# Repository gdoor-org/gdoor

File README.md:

<p align="center">
  https://gdoor-org.github.io/
</p>

_________________

The GDoor hardware adapter allows listening and controlling the bus and e.g. integrating a Gira door bell into a <b>smart home</b> like [Home Assistant](https://gdoor-org.github.io/documentation/homeassistant.html) or [openHAB](https://gdoor-org.github.io/documentation/openhab.html). It might serve as an DIY alternative to the Gira TKS-IP-Gateway. It supports the following features:

- (In development): Audio support via VOIP
- listening to the bus, e.g. to trigger notifications on mobile devices when a door bell button is pressed
- sending to the bus, e.g. to open the door

Receiving and sending video is currently neither supported nor plannend.

GDoor is a project to collect and document findings about the Gira Door System, all figured out by reverse engineering.
Contributions are welcome!

# Buy / DIY
Moved to the dedicated [page](https://gdoor-org.github.io/buy.html) on our homepage.

# Documentation / Home Automation
Moved to the dedicated [page](https://gdoor-org.github.io/documentation/getting-started.html) on our homepage.

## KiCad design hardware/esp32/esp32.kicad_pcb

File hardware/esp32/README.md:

More information about the firmware are located on the
[GDoor Homepage](https://gdoor-org.github.io/documentation/firmware.html).

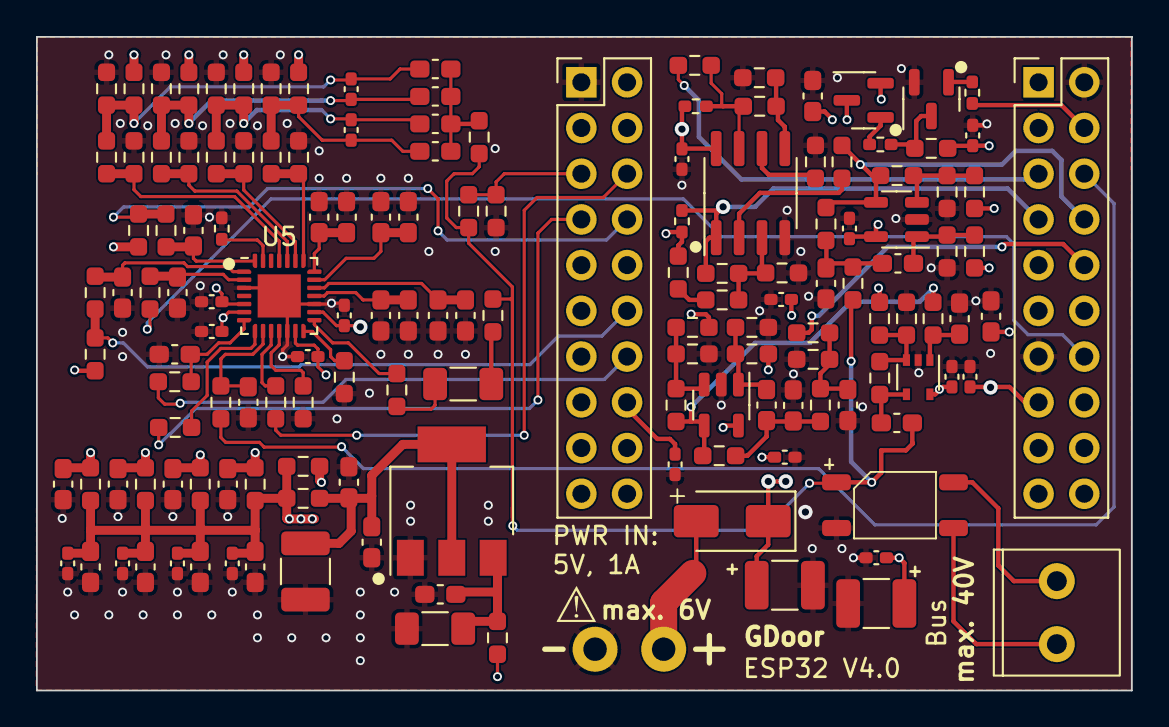
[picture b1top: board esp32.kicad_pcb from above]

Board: 4 copper layers, 60.8 x 36.3 mm, 151 parts (1 on the bottom side), 74 nets.

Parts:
C1: 47n; C_0603_1608Metric_Pad1.08x0.95mm_HandSolder
C2, C4, C8, C9, C18: 100p; C_0603_1608Metric_Pad1.08x0.95mm_HandSolder
C3, C5, C6, C7, C11, C13, C15, C16, C17, C36, C38, C40, C42, C46, C51, C53, C55, C62, C63: 100n; C_0402_1005Metric_Pad0.74x0.62mm_HandSolder
C10: 1n; C_0603_1608Metric_Pad1.08x0.95mm_HandSolder
C12, C14, C23, C25, C27, C28, C29, C30, C31, C35, C37, C39, C41, C43, C47, C52, C54, C56: 10u; C_0603_1608Metric_Pad1.08x0.95mm_HandSolder
C19, C20, C59: 100u; C_1210_3225Metric_Pad1.33x2.70mm_HandSolder
C21, C57: 10u; C_1206_3216Metric_Pad1.33x1.80mm_HandSolder
C22, C24, C26, C32, C33, C34: 100n; C_0603_1608Metric_Pad1.08x0.95mm_HandSolder
C44, C45, C48, C49, C50, C61: 22p; C_0603_1608Metric_Pad1.08x0.95mm_HandSolder
D1: MB10S; SOIC-4_4.55x3.7mm_P2.54mm
D2: SS14; D_SMA
J1: PlugIn_Terminal_Screw; anschlussklemme2x1_3_5
J2: ESP_left; PinHeader_2x10_P2.54mm_Vertical
J3: ESP_right; PinHeader_2x10_P2.54mm_Vertical
J4: PlugIn_Terminal_01x02; steckklemme2x1_dnp
Q1: MMBT5401; SOT-23
Q2: MMBT2222A; SOT-23
R1, R20: 130k; R_0603_1608Metric_Pad0.98x0.95mm_HandSolder
R2: 22k; R_0603_1608Metric_Pad0.98x0.95mm_HandSolder
R3, R4, R18, R19, R35: 82k; R_0603_1608Metric_Pad0.98x0.95mm_HandSolder
R5, R7, R16, R17: 5k1; R_0603_1608Metric_Pad0.98x0.95mm_HandSolder
R6, R10, R15, R22, R27, R33: 18k; R_0603_1608Metric_Pad0.98x0.95mm_HandSolder
R8, R13, R29, R31, R45: 10k; R_0402_1005Metric_Pad0.72x0.64mm_HandSolder
R9, R28, R30: 47k; R_0603_1608Metric_Pad0.98x0.95mm_HandSolder
R11, R23, R24, R73: 10k; R_0603_1608Metric_Pad0.98x0.95mm_HandSolder
R12, R25, R46, R47: 2k4; R_0603_1608Metric_Pad0.98x0.95mm_HandSolder
R14, R37, R38, R39, R40, R69, R70, R71, R72: 1k; R_0603_1608Metric_Pad0.98x0.95mm_HandSolder
R21, R26: 4k7; R_0603_1608Metric_Pad0.98x0.95mm_HandSolder
R32: 22; R_0603_1608Metric_Pad0.98x0.95mm_HandSolder
R34, R36, R55, R56, R57, R58, R59, R60, R61, R62, R63, R64, R65, R66, R67, R68, R74: 0; R_0603_1608Metric_Pad0.98x0.95mm_HandSolder
R41, R42, R43, R44, R50, R51, R52, R53, R54: 33; R_0603_1608Metric_Pad0.98x0.95mm_HandSolder
R48, R49: 100; R_0603_1608Metric_Pad0.98x0.95mm_HandSolder
S1: SYM_ESD_Small; ESD-Logo_6.6x6mm_SilkScreen
U: TLV9351; SOT-353_SC-70-5
U2, U3: LMV321; SOT-23-5
U4: ESP32_mini_no_pads
U5: ES8374; QFN-28-1EP_4x4mm_P0.45mm_EP2.4x2.4mm
U6: LM393; SOIC-8_3.9x4.9mm_P1.27mm
U7: AMS1117-3.3; SOT-223-3_TabPin2

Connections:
+3.3V: C6.1, C13.2, C14.2, C16.1, C17.1, C19.1, J2.16 (3V3), R3.2, R5.1, R25.1, R29.2, R31.2, R55.2, U2.5 (V+), U6.8 (V+)
+3.3V_ANA: C32.1, C59.1, C61.2, R58.2, U7.2 (VO)
+3.3V_AUDIO: C46.2, C47.2, C51.2, C52.2, C53.2, C54.2, C55.2, C56.2, R41.2, R42.2, R43.2, R44.2, R46.1, R47.1, R55.1, R58.1, R63.1, R64.1, R65.1, R66.1
+5V: C5.1, C11.2, C12.2, C20.1, D2.1 (K), J3.15 (VCC_(USB)), Q1.2 (E1), R9.2, R57.2
+5Vonoff: C3.1, C7.1, C15.1, Q1.3 (C1), R17.1, R18.2, R33.1, U.5 (V+), U3.5 (V+)
/BUS_DCVOLT: J2.5 (IO_39/SVN), R35.1, R73.1
/I2C_SCLK: J2.12 (IO_23/D7), R47.2, R48.1
/I2C_SDA: J2.8 (IO_18/D5), R46.2, R49.1
/I2S_ASDOUT: J2.7 (IO_35), R53.1
/I2S_DSDIN: J2.6 (IO_26/D0), R54.1
/I2S_LRCK: J3.6 (IO_25), R51.1
/I2S_MCLK: J3.14 (IO_00), R50.1
/I2S_SCLK: J2.14 (IO_05/D8), R52.1
/RX: J3.7 (IO_21/D2/SDA), R28.1, R29.1, U6.1
/RX_ANA: J3.8 (IO_32), R10.1, R12.1, R26.2, U2.4
/RX_DAC: J3.5 (IO_22/D1/SCL), R56.2
/TX: J3.10 (IO_12/TDI), R34.2
/TX_EN: J3.4 (IO_27), R13.2
GND: C2.1, C3.2, C5.2, C6.2, C7.2, C9.1, C10.1, C11.1, C12.1, C13.1, C14.1, C15.2, C16.2, C17.2, C18.1, C19.2, C20.2, C22.2, C23.1, C24.2, C25.1, C26.2, C27.1, C32.2, C33.2, C34.2, C35.1, C36.1, C37.1, C38.1, C39.1, C40.1, C41.1, C42.1, C43.1, C44.1, C45.1, C46.1, C47.1, C48.1, C49.1, C50.1, C51.1, C52.1, C53.1, C54.1, C55.1, C56.1, C57.1, C59.2, C61.1, D1.2 (-), J2.1 (GND), J3.2 (GND), J3.13 (GND), J4.1, Q2.2 (E), R4.1, R6.1, R7.1, R16.1, R19.1, R21.1, R22.2, R23.1, R27.2, R45.1, R59.1, R60.1, R61.1, R62.1, R67.1, R68.1, R69.1, R70.1, R71.1, R72.1, R73.2, U.2 (V-), U2.2 (V-), U3.2 (V-), U5.3 (DGND), U5.12 (SPKGND), U5.17 (AGND), U5.29 (EP), U6.4 (V-), U7.1 (GND)
unnamed: C1.1, R2.1, U.4
unnamed: C2.2, C4.2, R1.2, R10.2
unnamed: C8.2, C9.2, R15.2, R20.2
unnamed: C10.2, R20.1, R21.2, R34.1
unnamed: C21.1, R32.2
unnamed: C21.2, R36.1
unnamed: C28.1, C63.1, R37.1, R60.2, R63.2
unnamed: C28.2, C29.2, C30.2, C31.2, R74.2
unnamed: C29.1, C63.2, R38.1, R62.2, R66.2
unnamed: C30.1, C62.1, R39.1, R59.2, R64.2
unnamed: C31.1, C62.2, R40.1, R61.2, R65.2
unnamed: C1.2, D1.1 (+), R1.1, R35.2, R36.2, R74.1
unnamed: D2.2 (A), J4.2
unnamed: D1.4, J1.1
unnamed: D1.3, J1.2
unnamed: Q1.1 (B1), R8.1
unnamed: Q2.1 (B), R13.1
unnamed: Q2.3 (C), R8.2, R9.1
unnamed: R11.1, R14.1, R15.1, U3.4
unnamed: R24.2, R25.2
unnamed: R30.1, R31.1, R56.1, U6.7
unnamed: C18.2, R11.2, U.1 (+)
unnamed: R2.2, R6.2, R33.2, U.3 (-)
unnamed: C4.1, R3.1, R4.2, U2.1 (+)
unnamed: R5.2, R7.2, R12.2, U2.3 (-)
unnamed: C8.1, R18.1, R19.2, U3.1 (+)
unnamed: R14.2, R16.2, R17.2, U3.3 (-)
unnamed: C25.2, C26.1, U5.19 (ADCVREF)
unnamed: C27.2, C34.1, U5.18 (DACVREF)
unnamed: R37.2, R72.2, U5.24 (MIC1N)
unnamed: R38.2, R71.2, U5.25 (MIC1P)
unnamed: R39.2, R70.2, U5.22 (MIC2N)
unnamed: R40.2, R69.2, U5.23 (MIC2P)
unnamed: C22.1, C35.2, U5.21 (MICBIAS)
unnamed: R32.1, U5.15 (MONOOUT)
unnamed: R68.2, U5.11 (SPKN)
unnamed: R67.2, U5.14 (SPKP)
unnamed: C23.2, C24.1, U5.20 (VMID)
unnamed: C44.2, R48.2, U5.1 (CCLK)
unnamed: C45.2, R49.2, U5.28 (CDATA)
unnamed: R45.2, U5.27 (CE)
unnamed: R53.2, U5.8 (ASDOUT)
unnamed: R54.2, U5.10 (DSDIN)
unnamed: C49.2, R51.2, U5.9 (LRCK)
unnamed: C50.2, R50.2, U5.2 (MCLK)
unnamed: C48.2, R52.2, U5.7 (SCLK)
unnamed: C42.2, C43.2, R41.1, U5.16 (AVDD)
unnamed: C40.2, C41.2, R42.1, U5.6 (DVDD)
unnamed: C38.2, C39.2, R43.1, U5.5 (PVDD)
unnamed: C36.2, C37.2, R44.1, U5.13 (SPKVDD)
unnamed: R23.2, R24.1, R28.2, U6.3 (+)
unnamed: R26.1, U6.2 (-)
unnamed: R22.1, R30.2, U6.5 (+)
unnamed: R27.1, U6.6 (-)
unnamed: C33.1, C57.2, R57.1, U7.3 (VI)

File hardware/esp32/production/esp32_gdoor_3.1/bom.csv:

Designator,Footprint,Quantity,Value,LCSC Part #
C1,0603,1,47n,C1622
"C11, C13, C15, C16, C17, C3, C5, C6, C7",0402,9,100n,C307331
"C12, C14",0603,2,10u,C96446
"C19, C20",1210,2,100u,C15008
"C2, C4, C8, C9",0603,4,100p,C14858
D1,SOIC-4_4.55x3.7mm_P2.54mm,1,MB10S,C2488
D2,D_SMA,1,SS14,C2480
J1,steckklemme2x1_1,1,PlugIn_Terminal_01x02,C8387
J2,PinHeader_2x10_P2.54mm_Vertical,1,ESP_left,C7501280
J3,PinHeader_2x10_P2.54mm_Vertical,1,ESP_right,C7501280
J5,nofoorprint,1,Plugged into C8387,C8466
Q1,SOT-23,1,MMBT5401,C8326
Q2,SOT-23,1,MMBT2222A,C8512
"R1, R20",0603,2,130k,C22795
"R10, R15, R22, R33, R6",0603,5,18k,C25810
"R11, R23, R24",0603,3,10k,C25804
"R12, R25",0603,2,2k4,C22940
"R13, R29, R31, R8",0402,4,10k,C25744
R14,0603,1,1k,C21190
"R16, R17, R5, R7",0603,4,5k1,C23186
"R18, R19, R3, R4",0603,4,82k,C23254
R2,0603,1,22k,C31850
"R26, R27",0603,2,4k7,C23162
"R28, R30, R9",0603,3,47k,C25819
R32,0603,1,100k,C25803
R34,0603,1,0,C21189
U1,SOT-353_SC-70-5,1,TLV9351,C4367425
"U2, U3",SOT-23-5,2,LMV321,C7972
U6,SOIC-8_3.9x4.9mm_P1.27mm,1,LM393,C7955

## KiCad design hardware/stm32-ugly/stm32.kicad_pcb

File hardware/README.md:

# Content
> [!IMPORTANT]  
> Work in progress.
> The current hardware as shown here has a hardware bug:
> The high/low logic values of the ESP32 on the bus data receiving side are not
> respected. A comparator on Pin28 (GPIO32) is needed.
>
> The current firmware therefore decodes on Pin0 (IO12),
> as a manual hardware modification was added.

Simple adapter board for ESP32mini.
There are production files to get nearly fully assembled boards from http://jlcpcb.com under `esp32/production`.
A very rough guide how to order on http://jlcpcb.com is under https://www.youtube.com/watch?v=Y2G-SiKUJPk.

Additionally you will need:
- ESP32 Mini. E.g. from https://www.az-delivery.de/products/esp32-d1-mini
- 2x Stiftleiste 2,54mm 2x10 to solder into the adapter and connect the adapter PCB to the ESP32 Mini. E.g. https://www.reichelt.de/stiftleisten-2-54-mm-2x10-gerade-mpe-087-2-020-p119898.html

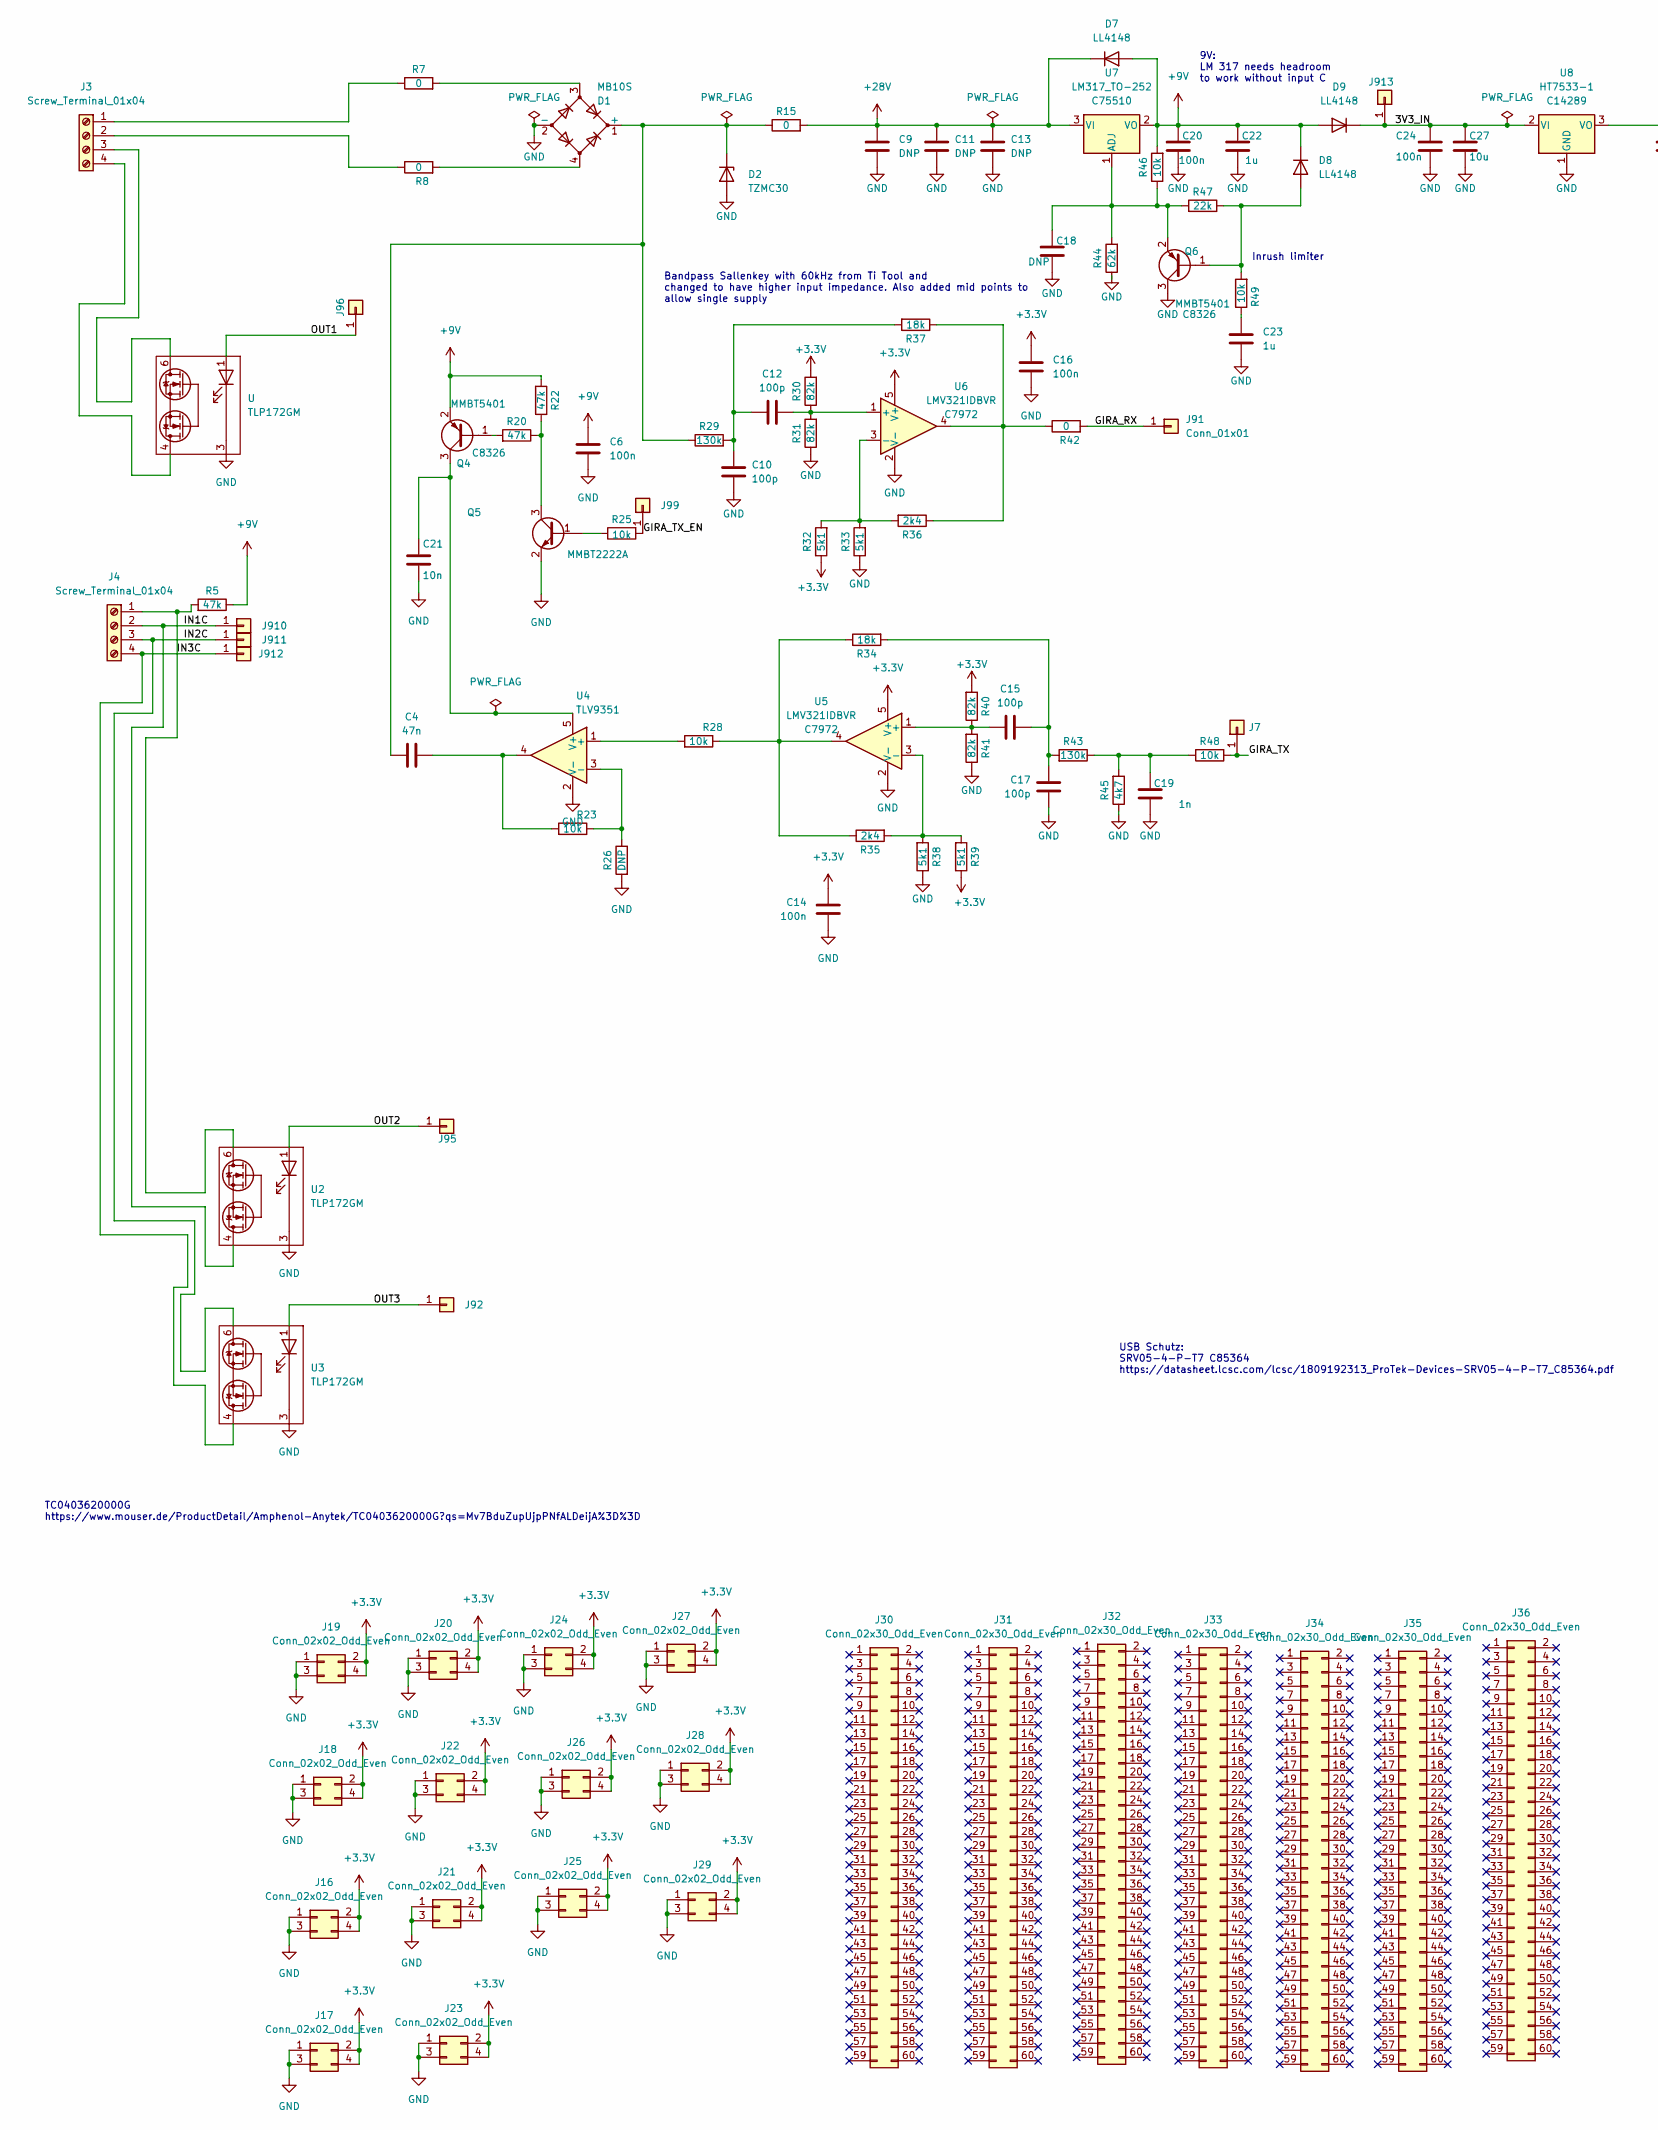
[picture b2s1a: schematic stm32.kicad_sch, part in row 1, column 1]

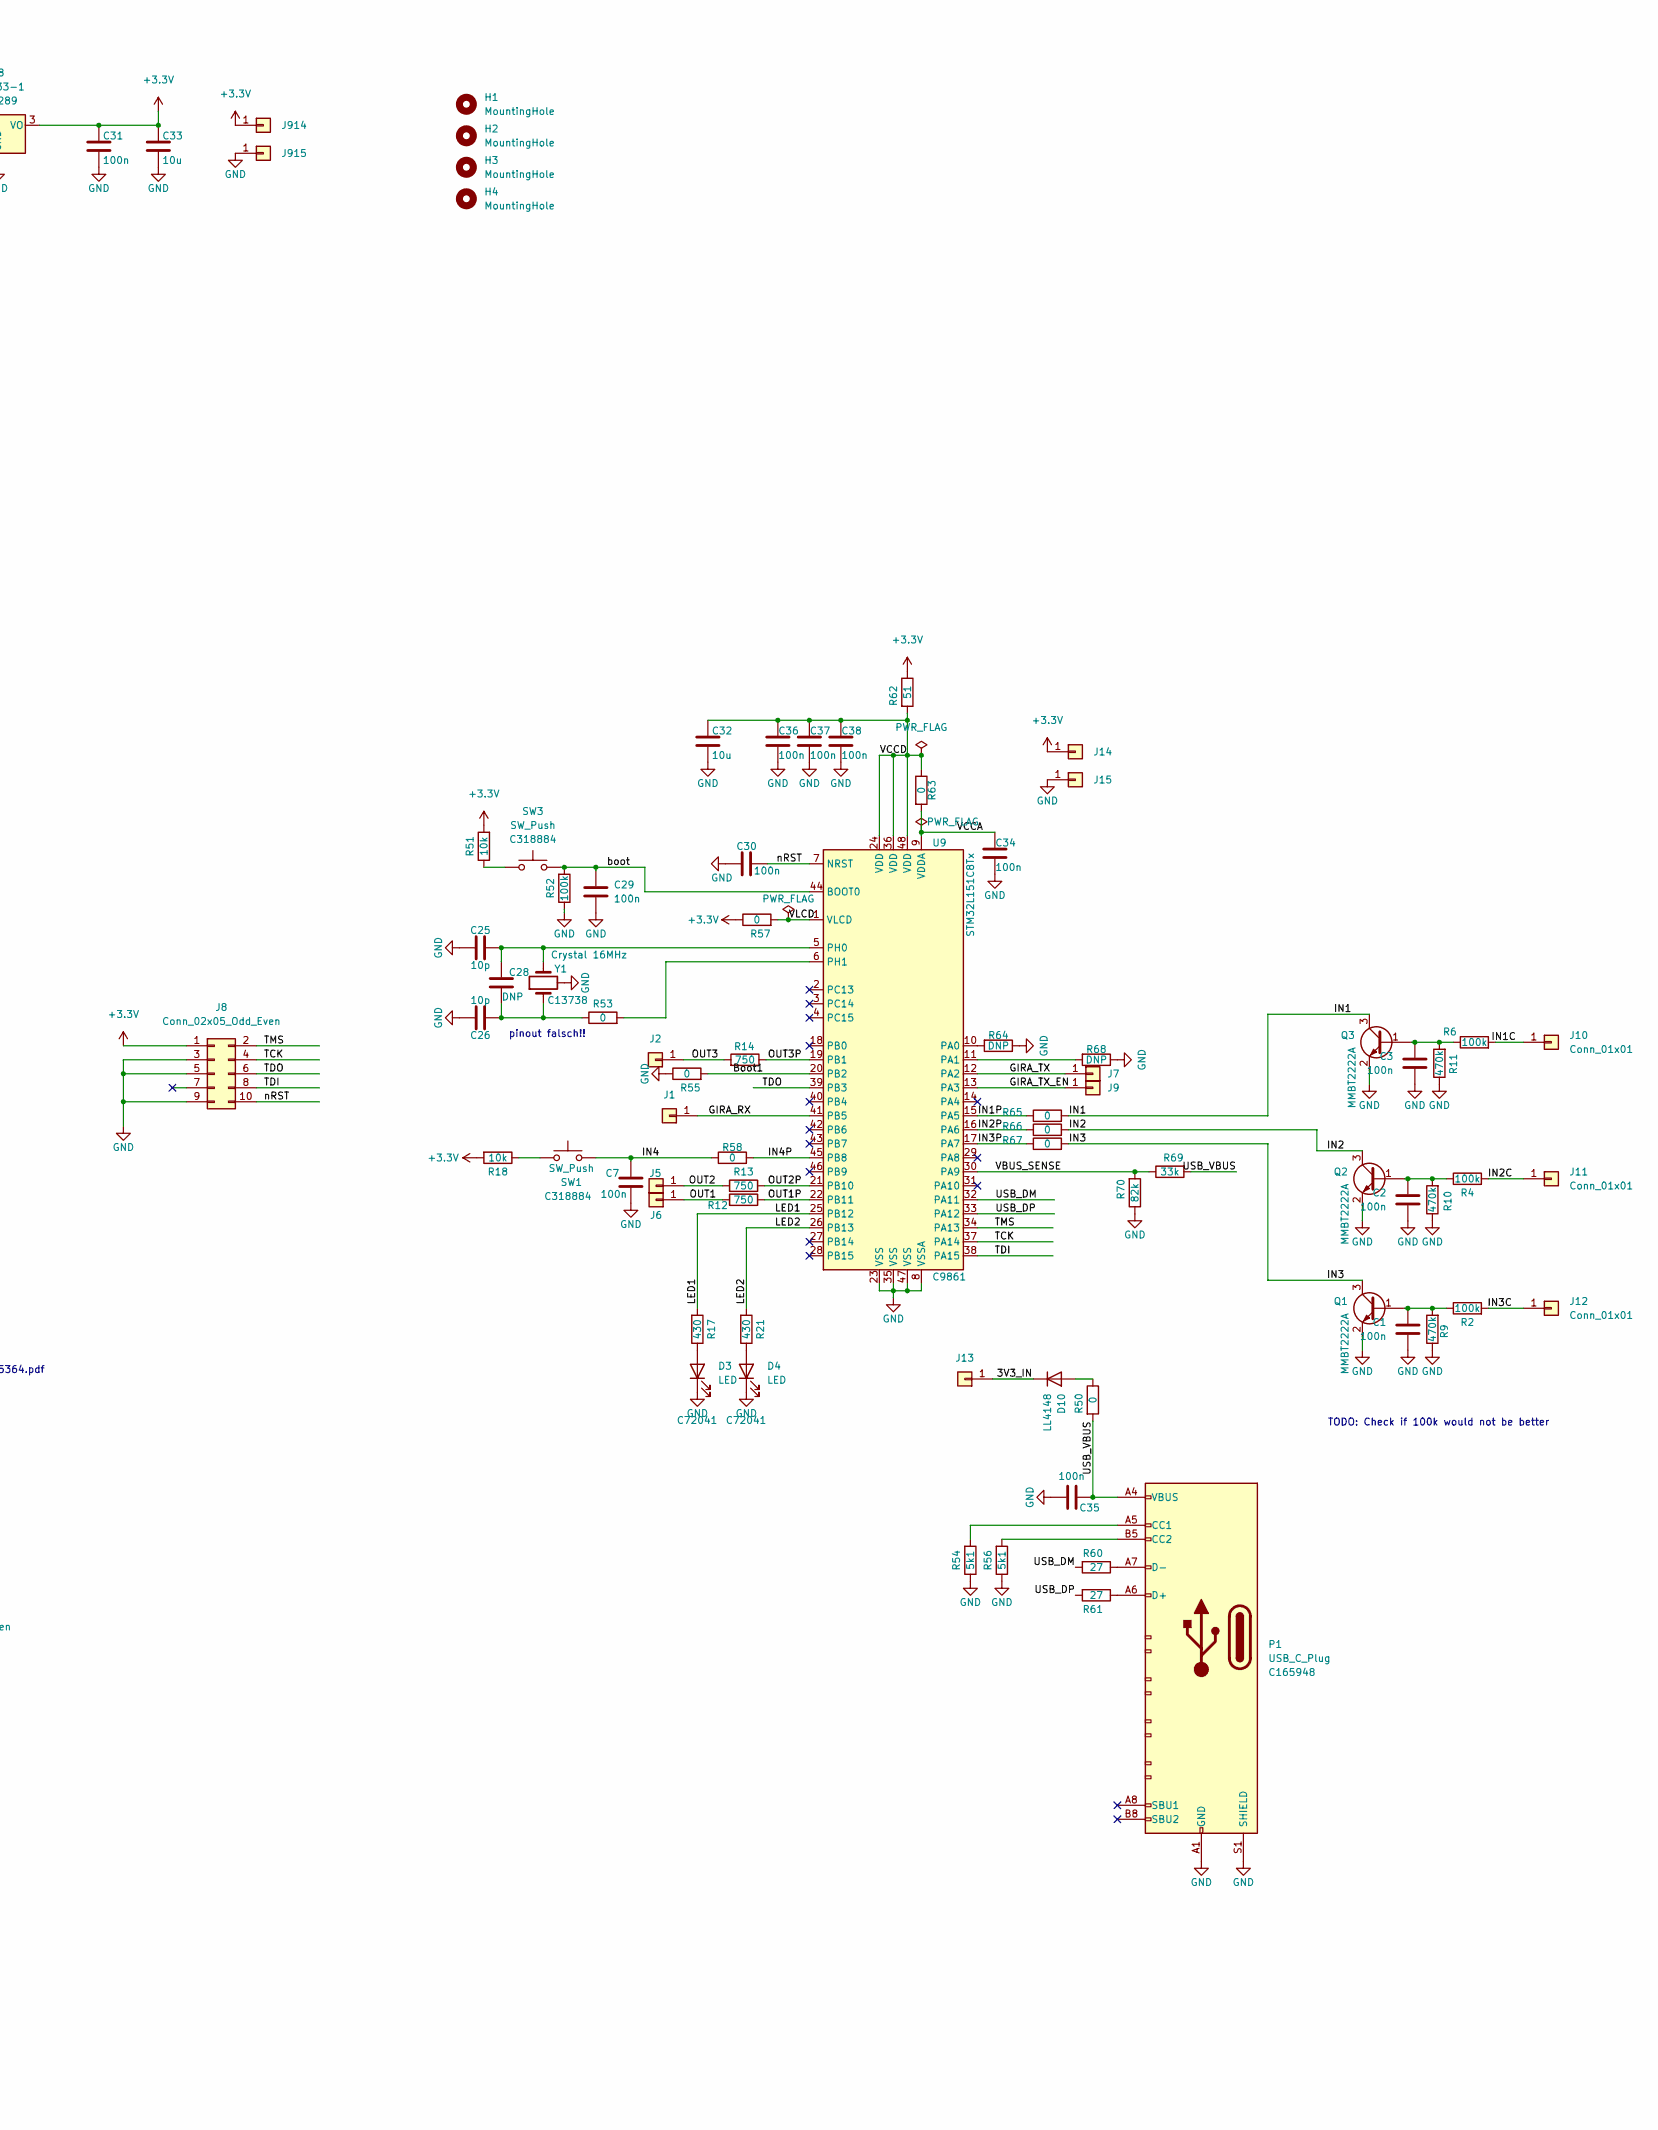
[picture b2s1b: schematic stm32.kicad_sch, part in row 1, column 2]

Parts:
C1, C2, C3, C6, C7, C14, C16, C20, C24, C29, C30, C31, C34, C35, C36, C37, C38: 100n; C_0603_1608Metric_Pad1.08x0.95mm_HandSolder; MPN C14663
C4: 47n; C_0603_1608Metric_Pad1.08x0.95mm_HandSolder; MPN C1622
C9, C11, C13, C18, C28: DNP; C_0603_1608Metric_Pad1.08x0.95mm_HandSolder; MPN DNP
C10, C12, C15, C17: 100p; C_0603_1608Metric_Pad1.08x0.95mm_HandSolder; MPN C14858
C19: 1n; C_0603_1608Metric_Pad1.08x0.95mm_HandSolder; MPN C1588
C21: 10n; C_0603_1608Metric_Pad1.08x0.95mm_HandSolder; MPN C57112
C22, C23: 1u; C_0603_1608Metric_Pad1.08x0.95mm_HandSolder; MPN C15849
C25, C26: 10p; C_0603_1608Metric_Pad1.08x0.95mm_HandSolder; MPN C1634
C27, C32, C33: 10u; C_0603_1608Metric_Pad1.08x0.95mm_HandSolder; MPN C96446
D1: MB10S; SOIC-4_4.55x3.7mm_P2.54mm; MPN C2488
D2: TZMC30; D_MiniMELF; MPN DNP
D3, D4: LED; LED_0603_1608Metric_Pad0.98x0.95mm_HandSolder; MPN C72041; JLCPCB C72041
D7, D8, D9, D10: LL4148; D_SOD-123; MPN C81598
H1, H2, H3, H4: MountingHole; MountingHole_2.7mm_M2.5_Pad_TopBottom; MPN DNP
J1, J2, J5, J6, J7, J9, J10, J11, J12, J13, J14, J15, J91, J92, J95, J96, J99, J910, J911, J912, J913, J914, J915: Conn_01x01; PinHeader_1x01_P2.54mm_Vertical
J3, J4: Screw_Terminal_01x04; anschlussklemme4x1; MPN DNP
J8: Conn_02x05_Odd_Even; PinHeader_2x05_P1.27mm_Vertical_SMD; MPN DNP
J16, J17, J18, J19, J20, J21, J22, J23, J24, J25, J26, J27, J28, J29: Conn_02x02_Odd_Even; PinHeader_2x02_P2.54mm_Vertical
J30, J31, J32, J33, J34, J35, J36: Conn_02x30_Odd_Even; PinHeader_2x30_P2.54mm_Vertical
P1: USB_C_Plug; USB_C_Receptacle_HRO_TYPE-C-31-M-12; MPN C165948; JLCPCB C165948
Q1, Q2, Q3, Q5: MMBT2222A; SOT-23; MPN C8512
Q4, Q6: MMBT5401; SOT-23; MPN C8326; JLCPCB C8326
R2, R4, R6, R52: 100k; R_0603_1608Metric_Pad0.98x0.95mm_HandSolder; MPN C25803
R5, R20, R22: 47k; R_0603_1608Metric_Pad0.98x0.95mm_HandSolder; MPN C25819
R7, R8, R15, R42, R50, R53, R55, R57, R58, R63, R65, R66, R67: 0; R_0603_1608Metric_Pad0.98x0.95mm_HandSolder; MPN C21189
R9, R10, R11: 470k; R_0603_1608Metric_Pad0.98x0.95mm_HandSolder; MPN C23178
R12, R13, R14: 750; R_0603_1608Metric_Pad0.98x0.95mm_HandSolder; MPN C23241
R17, R21: 430; R_0603_1608Metric_Pad0.98x0.95mm_HandSolder; MPN C23170
R18, R23, R25, R28, R46, R48, R49, R51: 10k; R_0603_1608Metric_Pad0.98x0.95mm_HandSolder; MPN C25804
R26, R64, R68: DNP; R_0603_1608Metric_Pad0.98x0.95mm_HandSolder; MPN DNP
R29, R43: 130k; R_0603_1608Metric_Pad0.98x0.95mm_HandSolder; MPN C22795
R30, R31, R40, R41, R70: 82k; R_0603_1608Metric_Pad0.98x0.95mm_HandSolder; MPN C23254
R32, R33, R38, R39, R54, R56: 5k1; R_0603_1608Metric_Pad0.98x0.95mm_HandSolder; MPN C23186
R34, R37: 18k; R_0603_1608Metric_Pad0.98x0.95mm_HandSolder; MPN C25810
R35, R36: 2k4; R_0603_1608Metric_Pad0.98x0.95mm_HandSolder; MPN C22940
R44: 62k; R_0603_1608Metric_Pad0.98x0.95mm_HandSolder; MPN C23221
R45: 4k7; R_0603_1608Metric_Pad0.98x0.95mm_HandSolder; MPN C23162
R47: 22k; R_0603_1608Metric_Pad0.98x0.95mm_HandSolder; MPN C31850
R60, R61: 27; R_0603_1608Metric_Pad0.98x0.95mm_HandSolder; MPN C25190
R62: 51; R_0603_1608Metric_Pad0.98x0.95mm_HandSolder
R69: 33k; R_0603_1608Metric_Pad0.98x0.95mm_HandSolder; MPN C4216
SW1, SW3: SW_Push; SW_SPST_TL3342; MPN C318884; JLCPCB C318884
U, U2, U3: TLP172GM; SO-6_4.4x3.6mm_P1.27mm; MPN DNP
U4: TLV9351; SOT-353_SC-70-5; MPN DNP
U5, U6: LMV321IDBVR; SOT-23-5; MPN C7972; JLCPCB C7972
U7: LM317_TO-252; TO-252-2; MPN C75510; JLCPCB C75510
U8: HT7533-1; SOT-89-3; MPN C14289; JLCPCB C14289
U9: STM32L151C8Tx; LQFP-48_7x7mm_P0.5mm; MPN C9861; JLCPCB C9861
Y1: Crystal 16MHz; Crystal_SMD_3225-4Pin_3.2x2.5mm; MPN C13738; JLCPCB C13738

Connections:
+3.3V: C14.1, C16.1, C31.2, C33.2, J8.1, J14.1, J16.2, J16.4, J17.2, J17.4, J18.2, J18.4, J19.2, J19.4, J20.2, J20.4, J21.2, J21.4, J22.2, J22.4, J23.2, J23.4, J24.2, J24.4, J25.2, J25.4, J26.2, J26.4, J27.2, J27.4, J28.2, J28.4, J29.2, J29.4, J914.1, R18.2, R30.2, R32.1, R39.1, R40.2, R51.2, R57.1, R62.1, U5.5 (V+), U6.5 (V+), U8.3 (VO)
+9V: C6.1, C20.2, C22.2, D7.2 (A), D8.1 (K), D9.2 (A), Q4.2 (E1), R5.1, R22.2, R46.2, U7.2 (VO)
+28V: C9.2, C11.2, C13.2, D7.1 (K), R15.2, U7.3 (VI)
/3V3_IN: C24.2, C27.2, D9.1 (K), D10.1 (K), J13.1, J913.1, U8.2 (VI)
/Boot1: R55.2, U9.20 (PB2)
/GIRA_RX: J1.1, J91.1, R42.2, U9.41 (PB5)
/GIRA_TX: J7.1, R48.2, U9.12 (PA2); also elsewhere on the board
/GIRA_TX_EN: J9.1, J99.1, R25.2, U9.13 (PA3)
/IN1: Q3.3 (C), R65.2
/IN1C: J4.2, J10.1, J910.1, R6.2, U2.4 (D)
/IN1P: R65.1, U9.15 (PA5)
/IN2: Q2.3 (C), R66.2
/IN2C: J4.3, J11.1, J911.1, R4.2, U3.6 (D)
/IN2P: R66.1, U9.16 (PA6)
/IN3: Q1.3 (C), R67.2
/IN3C: J4.4, J12.1, J912.1, R2.2, U3.4 (D)
/IN3P: R67.1, U9.17 (PA7)
/IN4: C7.2, R58.1, SW1.2
/IN4P: R58.2, U9.45 (PB8)
/LED1: R17.2, U9.25 (PB12)
/LED2: R21.2, U9.26 (PB13)
/OUT1: J6.1, J96.1, R12.2, U.1 (A)
/OUT1P: R12.1, U9.22 (PB11)
/OUT2: J5.1, J95.1, R13.2, U2.1 (A)
/OUT2P: R13.1, U9.21 (PB10)
/OUT3: J2.1, J92.1, R14.2, U3.1 (A)
/OUT3P: R14.1, U9.19 (PB1)
/TCK: J8.4, U9.37 (PA14)
/TDI: J8.8, U9.38 (PA15)
/TDO: J8.6, U9.39 (PB3)
/TMS: J8.2, U9.34 (PA13)
/USB_DM: R60.2, U9.32 (PA11)
/USB_DP: R61.2, U9.33 (PA12)
/USB_VBUS: C35.2, P1.A4 (VBUS), P1.A9 (VBUS), P1.B4 (VBUS), P1.B9 (VBUS), R50.2, R69.2
/VBUS_SENSE: R69.1, R70.2, U9.30 (PA9)
/VCCA: C34.2, R63.2, U9.9 (VDDA)
/VCCD: C32.2, C36.2, C37.2, C38.2, R62.2, R63.1, U9.24 (VDD), U9.36 (VDD), U9.48 (VDD)
/VLCD: R57.2, U9.1 (VLCD)
/boot: C29.2, R52.2, SW3.2, U9.44 (BOOT0)
/nRST: C30.2, J8.10, U9.7 (NRST)
GND: C1.2, C2.2, C3.2, C6.2, C7.1, C9.1, C10.1, C11.1, C13.1, C14.2, C16.2, C17.1, C18.1, C19.1, C20.1, C21.2, C22.1, C23.1, C24.1, C25.2, C26.2, C27.1, C29.1, C30.1, C31.1, C32.1, C33.1, C34.1, C35.1, C36.1, C37.1, C38.1, D1.2 (-), D2.2 (A), D3.K, D4.K, J8.3, J8.5, J8.9, J15.1, J16.1, J16.3, J17.1, J17.3, J18.1, J18.3, J19.1, J19.3, J20.1, J20.3, J21.1, J21.3, J22.1, J22.3, J23.1, J23.3, J24.1, J24.3, J25.1, J25.3, J26.1, J26.3, J27.1, J27.3, J28.1, J28.3, J29.1, J29.3, J915.1, P1.A1 (GND), P1.A12 (GND), P1.B1 (GND), P1.B12 (GND), P1.S1 (SHIELD), Q1.2 (E), Q2.2 (E), Q3.2 (E), Q5.2 (E), Q6.3 (C1), R9.1, R10.1, R11.1, R26.2, R31.1, R33.1, R38.1, R41.1, R44.1, R45.1, R52.1, R54.1, R55.1, R56.1, R64.1, R68.1, R70.1, U.3 (K), U2.3 (K), U3.3 (K), U4.2 (V-), U5.2 (V-), U6.2 (V-), U8.1 (GND), U9.8 (VSSA), U9.23 (VSS), U9.35 (VSS), U9.47 (VSS), Y1.3 (GND), Y1.4 (GND)
unnamed: C1.1, Q1.1 (B), R2.1, R9.2
unnamed: C2.1, Q2.1 (B), R4.1, R10.2
unnamed: C3.1, Q3.1 (B), R6.1, R11.2
unnamed: C4.1, R23.2, U4.4
unnamed: C4.2, D1.1 (+), D2.1 (K), R15.1, R29.1
unnamed: C10.2, C12.2, R29.2, R37.2
unnamed: C12.1, R30.1, R31.2, U6.1 (+)
unnamed: C15.1, R40.1, R41.2, U5.1 (+)
unnamed: C15.2, C17.2, R34.2, R43.2
unnamed: C18.2, Q6.2 (E1), R44.2, R46.1, R47.2, U7.1 (ADJ)
unnamed: C19.2, R43.1, R45.2, R48.1
unnamed: C21.1, Q4.3 (C1), U4.5 (V+)
unnamed: C23.2, R49.1
unnamed: C25.1, C28.1, U9.5 (PH0), Y1.2
unnamed: C26.1, C28.2, R53.1, Y1.1
unnamed: D1.3, R7.2
unnamed: D1.4, R8.2
unnamed: D3.A, R17.1
unnamed: D4.A, R21.1
unnamed: D8.2 (A), Q6.1 (B1), R47.1, R49.2
unnamed: D10.2 (A), R50.1
unnamed: J3.1, R7.1
unnamed: J3.2, R8.1
unnamed: J3.3, U.6 (D)
unnamed: J3.4, U.4 (D)
unnamed: J4.1, R5.2, U2.6 (D)
unnamed: P1.A5 (CC1), R54.2
unnamed: P1.A6 (D+), P1.B6 (D+), R61.1
unnamed: P1.A7 (D-), P1.B7 (D-), R60.1
unnamed: P1.B5 (CC2), R56.2
unnamed: Q4.1 (B1), R20.2
unnamed: Q5.1 (B), R25.1
unnamed: Q5.3 (C), R20.1, R22.1
unnamed: R18.1, SW1.1
unnamed: R23.1, R26.1, U4.3 (-)
unnamed: R28.1, R34.1, R35.1, U5.4
unnamed: R28.2, U4.1 (+)
unnamed: R32.2, R33.2, R36.2, U6.3 (-)
unnamed: R35.2, R38.2, R39.2, U5.3 (-)
unnamed: R36.1, R37.1, R42.1, U6.4
unnamed: R51.1, SW3.1
unnamed: R53.2, U9.6 (PH1)
unnamed: R64.2, U9.10 (PA0)
unnamed: R68.2, U9.11 (PA1)

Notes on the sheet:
Inrush limiter
Bandpass Sallenkey with 60kHz from Ti Tool and changed to have higher input impedance. Also added mid points to allow single supply
9V: LM 317 needs headroom to work without input C
pinout falsch!!
USB Schutz: SRV05-4-P-T7 C85364 https://datasheet.lcsc.com/lcsc/1809192313_ProTek-Devices-SRV05-4-P-T7_C85364.pdf
TODO: Check if 100k would not be better
TC0403620000G https://www.mouser.de/ProductDetail/Amphenol-Anytek/TC0403620000G?qs=Mv7BduZupUjpPNfALDeijA%3D%3D

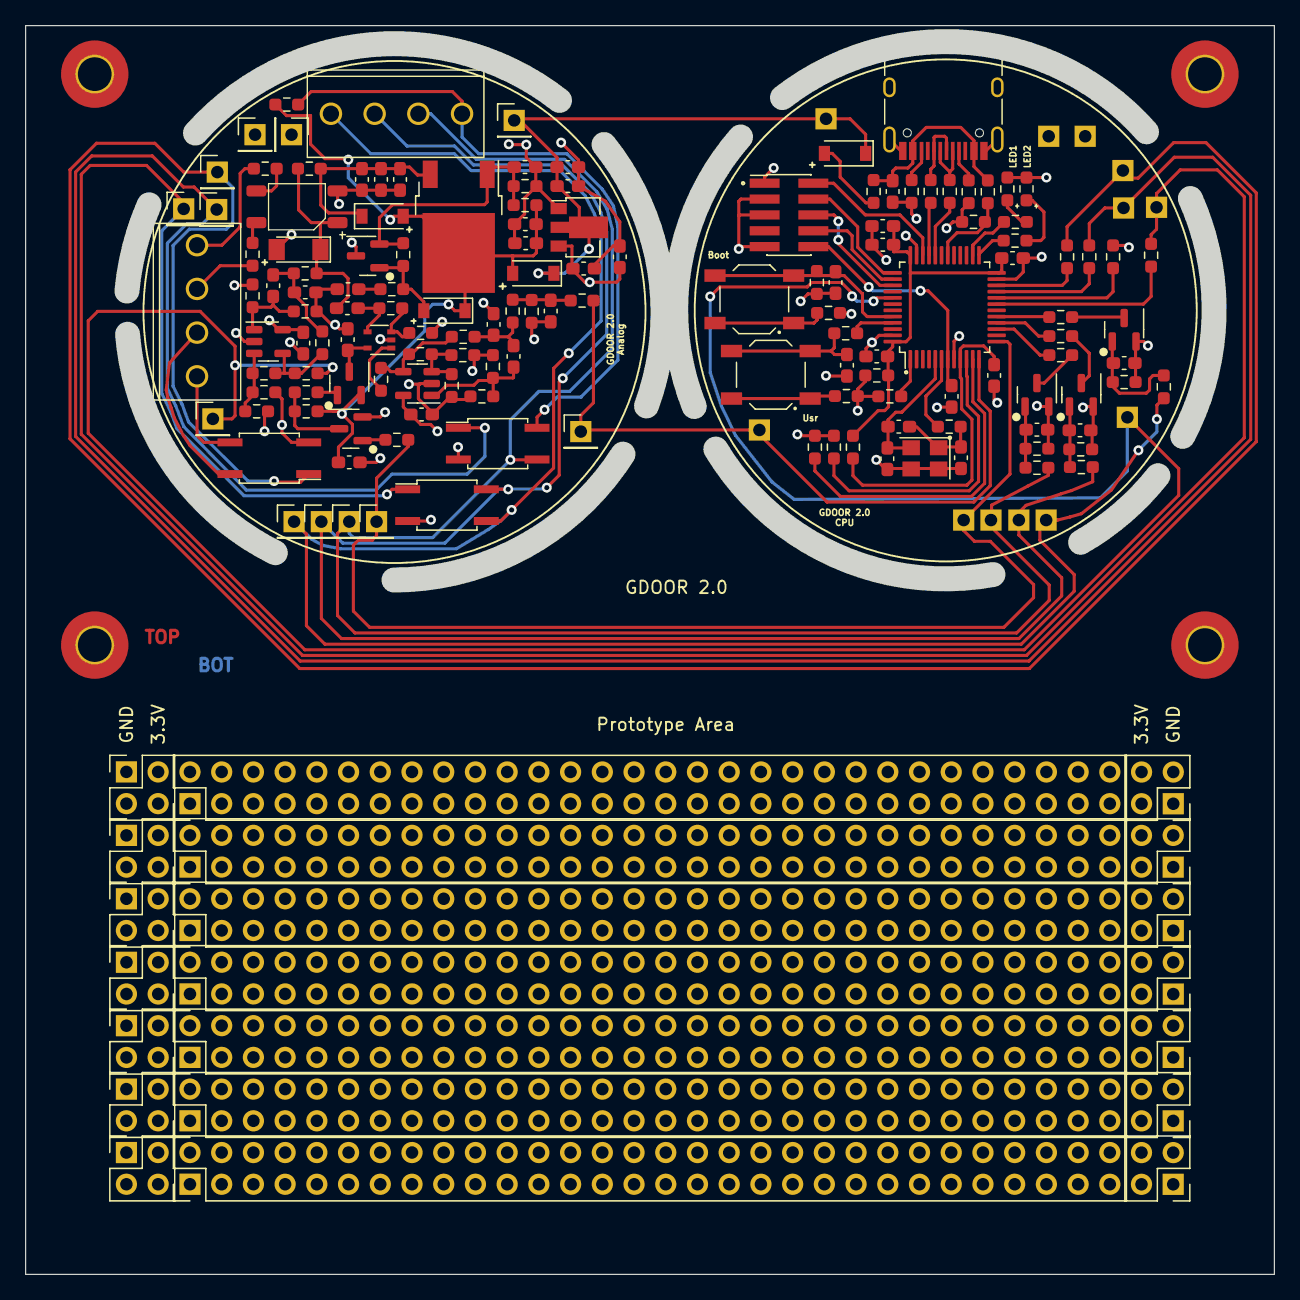
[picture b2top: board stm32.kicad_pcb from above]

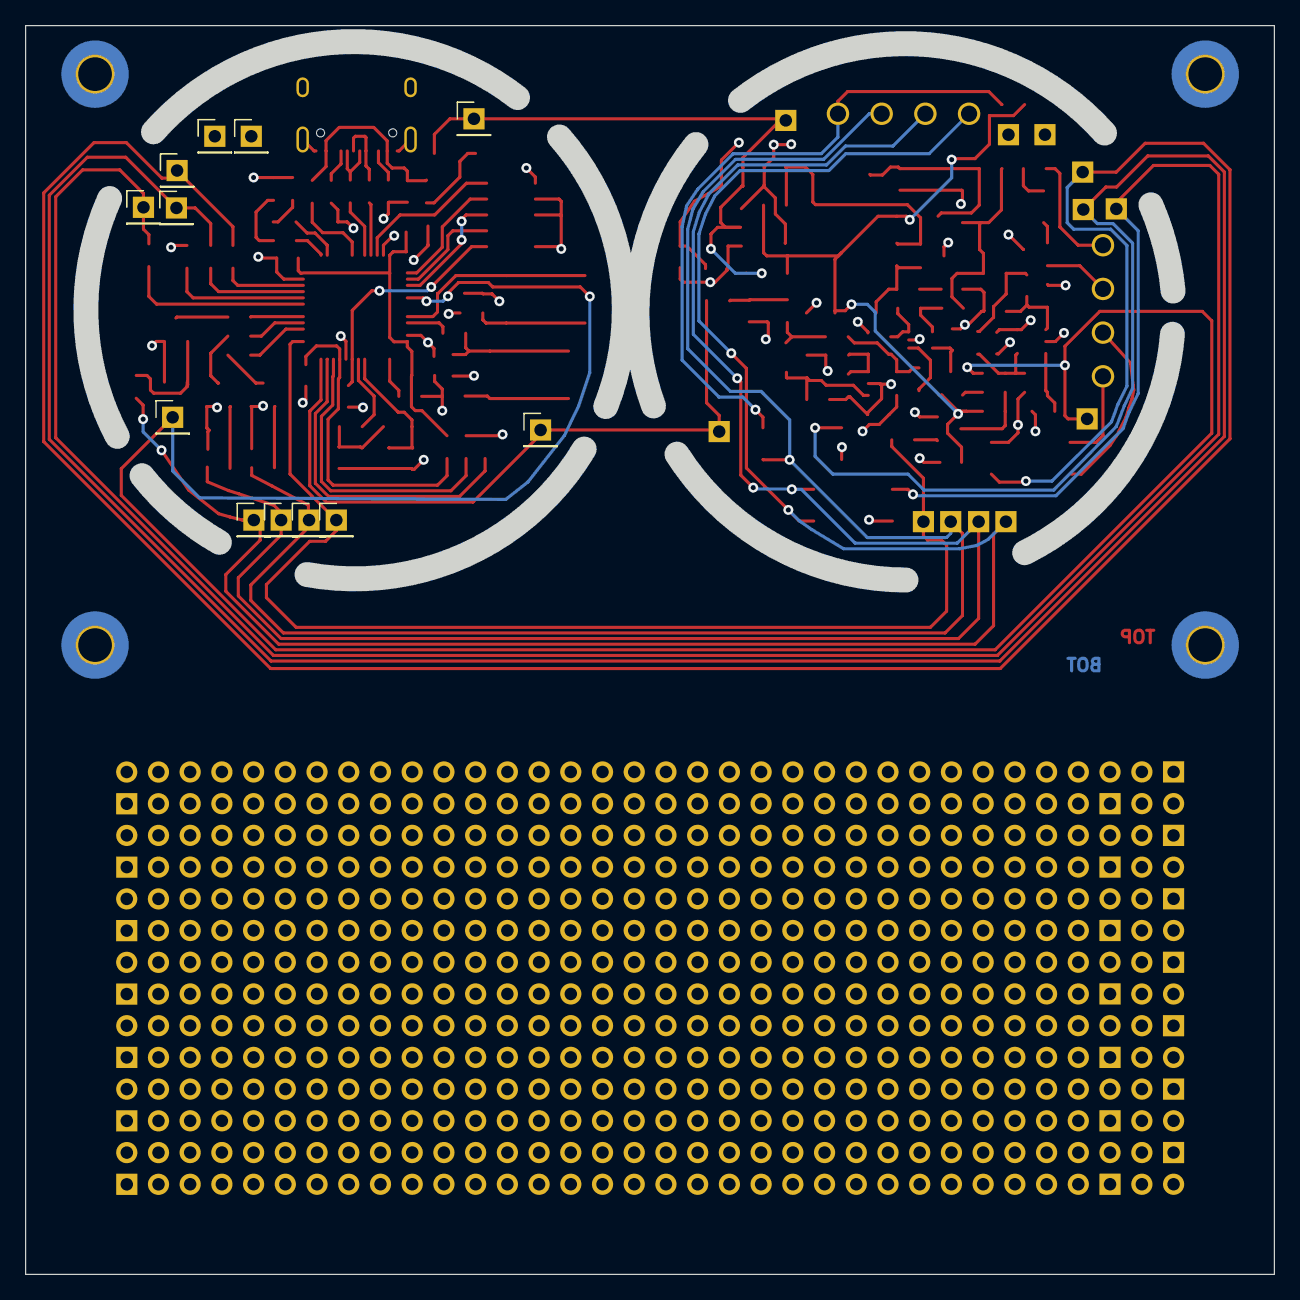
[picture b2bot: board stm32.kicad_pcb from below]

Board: 4 copper layers, 100.0 x 100.0 mm, 178 parts (12 on the bottom side), 85 nets.

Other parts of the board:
J7#2: Conn_01x01; PinHeader_1x01_P2.54mm_Vertical

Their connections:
/GIRA_TX: J7#2.1; also elsewhere on the board

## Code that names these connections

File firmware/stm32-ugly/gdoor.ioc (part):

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Mcu.Name=STM32L151C(6-8-B)Tx
Mcu.Package=LQFP48
Mcu.UserName=STM32L151C8Tx
PA11.Mode=Device
PA11.Signal=USB_DM
PA12.Mode=Device
PA12.Signal=USB_DP
PA13.Mode=JTAG_4_pins
PA13.Signal=SYS_JTMS-SWDIO
PA14.Mode=JTAG_4_pins
PA14.Signal=SYS_JTCK-SWCLK
PA15.Mode=JTAG_4_pins
PA15.Signal=SYS_JTDI
PA2.GPIOParameters=GPIO_Speed,GPIO_Label
PA2.GPIO_Label=PIN_GIRA_TX
PA2.GPIO_Speed=GPIO_SPEED_FREQ_VERY_HIGH
PA2.Signal=S_TIM2_CH3
PA3.GPIOParameters=GPIO_Label
PA3.GPIO_Label=PIN_GIRA_TX_EN
PA3.Signal=GPIO_Output
PA4.Signal=COMP_DAC1_group
PA5.GPIOParameters=GPIO_PuPd,GPIO_Label
PA5.GPIO_Label=PIN_IN1
PA5.GPIO_PuPd=GPIO_PULLUP
PA5.Signal=GPIO_Input
PA6.GPIOParameters=GPIO_PuPd,GPIO_Label
PA6.GPIO_Label=PIN_IN2
PA6.GPIO_PuPd=GPIO_PULLUP
PA6.Signal=GPIO_Input
PA7.GPIOParameters=GPIO_PuPd,GPIO_Label
PA7.GPIO_Label=PIN_IN3
PA7.GPIO_PuPd=GPIO_PULLUP
PA7.Signal=GPIO_Input
PB1.GPIOParameters=GPIO_PuPd,GPIO_Label
PB1.GPIO_Label=PIN_OUT3
PB1.GPIO_PuPd=GPIO_NOPULL
PB1.Signal=GPIO_Output
PB10.GPIOParameters=GPIO_Label
PB10.GPIO_Label=PIN_OUT2
PB10.Signal=GPIO_Output
PB11.GPIOParameters=GPIO_Label
PB11.GPIO_Label=PIN_OUT1
PB11.Signal=GPIO_Output
PB12.GPIOParameters=GPIO_Label
PB12.GPIO_Label=PIN_LED1
PB12.Signal=GPIO_Output
PB13.GPIOParameters=GPIO_Label
PB13.GPIO_Label=PIN_LED2
PB13.Signal=GPIO_Output
PB3.Mode=JTAG_4_pins
PB3.Signal=SYS_JTDO-TRACESWO
PB5.GPIOParameters=GPIO_Label
PB5.GPIO_Label=PIN_GIRA_RX
PB5.Mode=INP
PB5.Signal=COMP2_INP
PB8.GPIOParameters=GPIO_PuPd,GPIO_Label
PB8.GPIO_Label=PIN_IN4
PB8.GPIO_PuPd=GPIO_PULLDOWN
PB8.Signal=GPXTI8
PH0-OSC_IN.Mode=HSE-External-Oscillator
PH0-OSC_IN.Signal=RCC_OSC_IN
PH1-OSC_OUT.Mode=HSE-External-Oscillator
PH1-OSC_OUT.Signal=RCC_OSC_OUT
RCC.HSE_VALUE=16000000
RCC.SYSCLKFreq_VALUE=16000000
RCC.SYSCLKSource=RCC_SYSCLKSOURCE_HSE
board=custom
